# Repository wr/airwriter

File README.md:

# AirWriter

AirPrint for your vintage Apple printer.

Print from your phone or computer to an Apple ImageWriter, StyleWriter or LaserWriter. Connect
AirWriter to the printer and your Wi-Fi, and the printer shows up like any other. Nothing to
install.

The top is a gold-plated circuit board with 37 lights glowing through it. A rainbow sweeps
across when it starts up, and a few dots glow like fireflies while it's idle.

- **Five-minute setup.** All from your phone.
- **Color.** If your printer does color, so does AirWriter.
- **Vintage Macs too.** Print from a vintage Mac over a LocalTalk cable or your network, or from
  an emulator like Infinite Mac.
- **Up to six printers.** One AirWriter shares them all.
- **Open source.** Hardware and software, free to tinker with.

Buy one from [Wells Workshop](https://shop.wells.ee/products/airwriter).

## What you need

- A vintage Apple printer ([check yours](../../wiki/Supported-Printers))
- The cable your printer uses with a Mac ([which cable](../../wiki/Troubleshooting#crossover-cable))
- A USB-C charger
- 2.4 GHz Wi-Fi

The [wiki](../../wiki) has setup help and troubleshooting. [Updates](../../releases) install over
Wi-Fi.

Questions? Ask in [Wells Workshop on Discord](https://discord.gg/gACNgfyB7k), where other builders can help too. Found a bug or want a feature? Open an [issue](https://github.com/wr/airwriter/issues).

## How it works

Inside is an ESP32-S3. It shows each printer to your network as an AirPrint printer. Each page
goes out in the printer's own language, down the printer cable or over AppleTalk. LocalTalk runs
on Tashtari's TashTalk, on a small PIC chip.

| Path | Contents |
|---|---|
| `firmware/` | ESP-IDF application (ESP32-S3) |
| `tools/` | Host builds of the raster and IPP code, tests, fixtures and the settings page |
| `hardware/` | KiCad board and front panel |
| `enclosure/` | Case and light-guide lattice in build123d, with printable STLs in `out/` |

Firmware builds with ESP-IDF 5.5 (`idf.py -C firmware build`). Host tests run anywhere with a C
compiler: `make -C tools/rip test regress` and `make -C tools/ipp test`. `AGENTS.md` has the full
toolchain notes.

## Credits

LocalTalk runs on Tashtari's [TashTalk](https://github.com/lampmerchant/tashtalk). Monroe
Williams worked out the StyleWriter's serial protocol in the 1990s and wrote
[lpstyl](https://github.com/Godzil/lpstyl). FeralFirmware took Apple's StyleWriter and LaserWriter 300
drivers apart for [TailTalk](https://github.com/FeralFirmware/TailTalk) and InkTalk. Thank you all.

## License

Firmware and tools are GPL-3.0-or-later, hardware and enclosure CERN-OHL-S-2.0, docs CC-BY-SA-4.0.
See [`LICENSE.md`](LICENSE.md), which also covers third-party material.

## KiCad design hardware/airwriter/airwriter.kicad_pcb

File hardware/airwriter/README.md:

# AirWriter hardware

KiCad 10 project. Two-layer, 1.6mm FR4, 1oz copper, HASL.

**Board is 32 x 54mm.** The spec targeted 55 x 35mm (1925mm²); this is 1728mm².
Three parts set the floor and none of them can shrink:

- the ESP32-S3-WROOM-1 needs 18 x 19.5mm of board with its antenna overhanging the top edge
- the mini-DIN body reserves the entire bottom 13.5mm
- the USB-C receptacle sits beside it on the same edge

## Status

| Stage | State |
|---|---|
| Schematic | Complete. ERC clean, zero errors. 52 footprints, both ports. |
| Routing | Complete. 434 segments, 34 vias. **Every component pad connected.** |
| DRC | 5, all cosmetic. 15 unconnected, all pour-fragment to pour-fragment, none involving a pad or track. |
| Fab outputs | Gerbers, Excellon drill + map, BOM, pick-and-place, render, in `fab/`. |

Board is **52 x 54mm**, two layers. Bottom edge carries the printer mini-DIN, the
LocalTalk mini-DIN and USB-C. BOM is 44 populated parts plus 4 DNP.

### What DRC still reports, and why it is fine

- 2 silkscreen-over-edge on U1. The module deliberately overhangs the top edge.
- 3 library metadata mismatches. J2 and J4 because the mini-DIN footprint was injected
  into the board by hand; U1 because its thermal-via drills were deliberately enlarged.
- 15 "unconnected" between GND pour fragments. Every fragment is anchored to GND through
  an adjacent pad or via, so this is zone contiguity rather than floating copper. **No pad
  and no track appears in the unconnected list.**

## Modes

The board supports three, and only the third needed hardware:

1. **AirPrint only** — IPP over WiFi to the printer's serial port.
2. **AirPrint + EtherTalk** — pure firmware, no hardware change. Not yet written.
3. **AirPrint + LocalTalk** — the second mini-DIN, the PIC running TashTalk, and the split
   transceiver. This is AirWriter acting as the AppleTalk option card the ImageWriter never
   had. Firmware not yet written.

Only one AppleTalk transport can be active at a time unless you write an AppleTalk router.
AirPrint runs concurrently with any of them because it is IP.

## Routing

Routed with Freerouting 2.2.4. It cannot be automated: KiCad 10 dropped Specctra DSN export and
SES import from `kicad-cli`, so the round trip is GUI-only. Freerouting lives at
`~/.local/share/freerouting/freerouting.jar` and Java 25 is present. To re-route:

1. Open the PCB, File > Export > Specctra DSN
2. `java -jar ~/.local/share/freerouting/freerouting.jar -de board.dsn -do board.ses`
3. File > Import > Specctra Session

**After any re-route, always run DRC with `--refill-zones`.** Freerouting does not repour the GND
zone, and an unfilled zone produces hundreds of phantom clearance errors — 278 violations that
drop to 3 once refilled.

## Fab: PCBWay

Order as: **32 x 54mm, 2 layer, 1.6mm FR4, 1oz copper, HASL**. Nothing here needs a premium
process.

The design is held to PCBWay's cost-effective tier on purpose:

| Parameter | This board | PCBWay |
|---|---|---|
| Min drill | 0.30mm | 0.30mm standard. **0.20mm is an upgraded spec and costs a lot more** |
| Min track / space | 0.20mm actual, 0.15mm rule | 0.076mm possible, 0.15mm recommended to save cost |
| Copper to board edge | 0.2665mm worst case | under 0.20mm gets flagged |
| Via | 0.6mm pad / 0.3mm drill | standard |

**The 0.30mm drill floor is the one to protect.** KiCad's stock ESP32-S3-WROOM-1 footprint puts
twelve 0.20mm thermal vias in its ground pad, which would drop the whole board into PCBWay's
advanced tier — a documented case went from $5 to $65 for ten boards. Those twelve drills were
enlarged to 0.30mm in the board file. The 0.6mm pad still leaves a 0.15mm annular ring.

That edit lives in the board, not in KiCad's library, so **re-importing U1's footprint from the
library will silently put the 0.20mm drills back**. It is also why U1 shows a library mismatch in
DRC. Check the drill table before every order:

```
kicad-cli pcb export drill --output fab/ --format excellon airwriter.kicad_pcb
grep -E '^T[0-9]+C' fab/airwriter.drl     # nothing below 0.300
```

BOM carries manufacturer part numbers for the actives and connectors. Passives are specified by
value, package, dielectric and voltage with "or equivalent", which PCBWay sources normally.

## Toolchain notes

`kicad-cli` is not on PATH: `/Applications/KiCad/KiCad.app/Contents/MacOS/kicad-cli` (10.0.2).

Three traps hit while building this, all worth remembering:

- **`set_design_rules` (konnect MCP) corrupts this board.** KiCad 10 keeps DRC constraints in
  `.kicad_pro`, but the tool writes them into the `.kicad_pcb` setup block, duplicating keys and
  making the board unloadable. Edit `airwriter.kicad_pro` instead.
- **`set_board_size` appends an outline rather than replacing it.** Calling it twice leaves two
  overlapping rectangles on Edge.Cuts.
- **The konnect placement tools resolve `lib_id` only against KiCad's install directory**, ignoring
  project and global library tables. The project libraries are symlinked into the app bundle as a
  workaround; those symlinks vanish on a KiCad upgrade and need recreating.

`min_through_hole_diameter` is set to 0.2mm because the WROOM-1 footprint uses 0.2mm thermal vias
in its ground pad. That is within JLCPCB capability.

## Deviations from the spec

- **U2 is a MAX3490ESA+ (SOIC-8), not a MAX3491ESD+ (SOIC-14).** The spec tied DE high and RE low
  permanently, so the MAX3491's enable pins were dead weight. The MAX3490 is the same full-duplex
  RS-422 transceiver without them, and it ships with a verified pinout in KiCad's stock library.
- **No polarity jumpers at all.** The spec wanted them so the RS-422 pairs could be swapped
  without a respin. The ESP32 UART does the same job in firmware — `uart_set_line_inverse()`
  with `UART_SIGNAL_TXD_INV` / `UART_SIGNAL_RXD_INV`. Inverting DI flips Y and Z together,
  which is electrically identical to swapping the pair. Four parts saved, insurance kept.
- **Receiver polarity corrected.** Spec 2.4 mapped A<-TxD- and B<-TxD+, which inverts every
  received byte. Apple's convention is that a binary 1 has TxD- more negative than TxD+, so
  the + line is non-inverting: A<-TxD+ (pin 6), B<-TxD- (pin 3).
- **R9 added**, a DNP 0R in series with the MAX3232 T1OUT to HSKi path. The spec wanted T1 wired
  but not populated; a DNP series resistor expresses that without U3 driving HSKi by default.
- **SW1 is a B3U-1000P**, not the 4.5mm tactile the spec assumed. The B3S-1100 KiCad offers has a
  10 x 8.9mm courtyard which had become the binding constraint on the pocket beside the mini-DIN.

## Custom library

`lib/airwriter.kicad_sym` and `lib/airwriter.pretty` hold the two parts KiCad does not ship:

- `MiniDIN-8_Kycon_KMDGX-8S-BS_RightAngle` — KiCad has no mini-DIN footprint at all. Geometry taken
  from Kycon engineering drawing KMDGX-xS-BS rev C6 (ECO#18-013), 8-position "Recommended PCB
  Layout (Top View)". Note pin 7 sits at +0.90mm from the centreline while pin 2 directly above it
  sits at +1.30mm — the lower row is deliberately asymmetric.
- `Mini-DIN-8_Shielded` — the stock symbol has no shield pin, so there is no way to net the shell
  for the 0R + 1nF star ground. Pin 9 is SHIELD, tied to all three mounting posts.

## Still to do

1. Add LCSC/Digi-Key ordering codes to the BOM. It currently carries values and footprints only.
2. Optional: 3mm corner radii, which the spec asked for and the outline does not yet have.

## Traps that cost real time here

- **The GND zone was on net `"GND"` while every pad is on `"/GND"`.** KiCad uses the hierarchical
  name with a leading slash. The pour was floating for its entire life and DRC reported it as 28
  isolated-copper islands rather than as a disconnected zone. Check zone nets by string.
- **Footprint zones store absolute coordinates.** Moving a footprint by editing `(at ...)` in a
  script moves the pads but strands any keepout polygon. The WROOM-1 antenna keepout sat 46mm off
  the board until corrected, so DRC was never enforcing it.
- **Freerouting does not repour zones.** Always DRC with `--refill-zones`.

## Trademarks

AirPrint, AppleTalk, LocalTalk, EtherTalk and ImageWriter are trademarks of Apple Inc.
AirWriter is an independent project and is not affiliated with, authorised, sponsored or
endorsed by Apple Inc. These marks are used only descriptively, to state what the board
interoperates with.

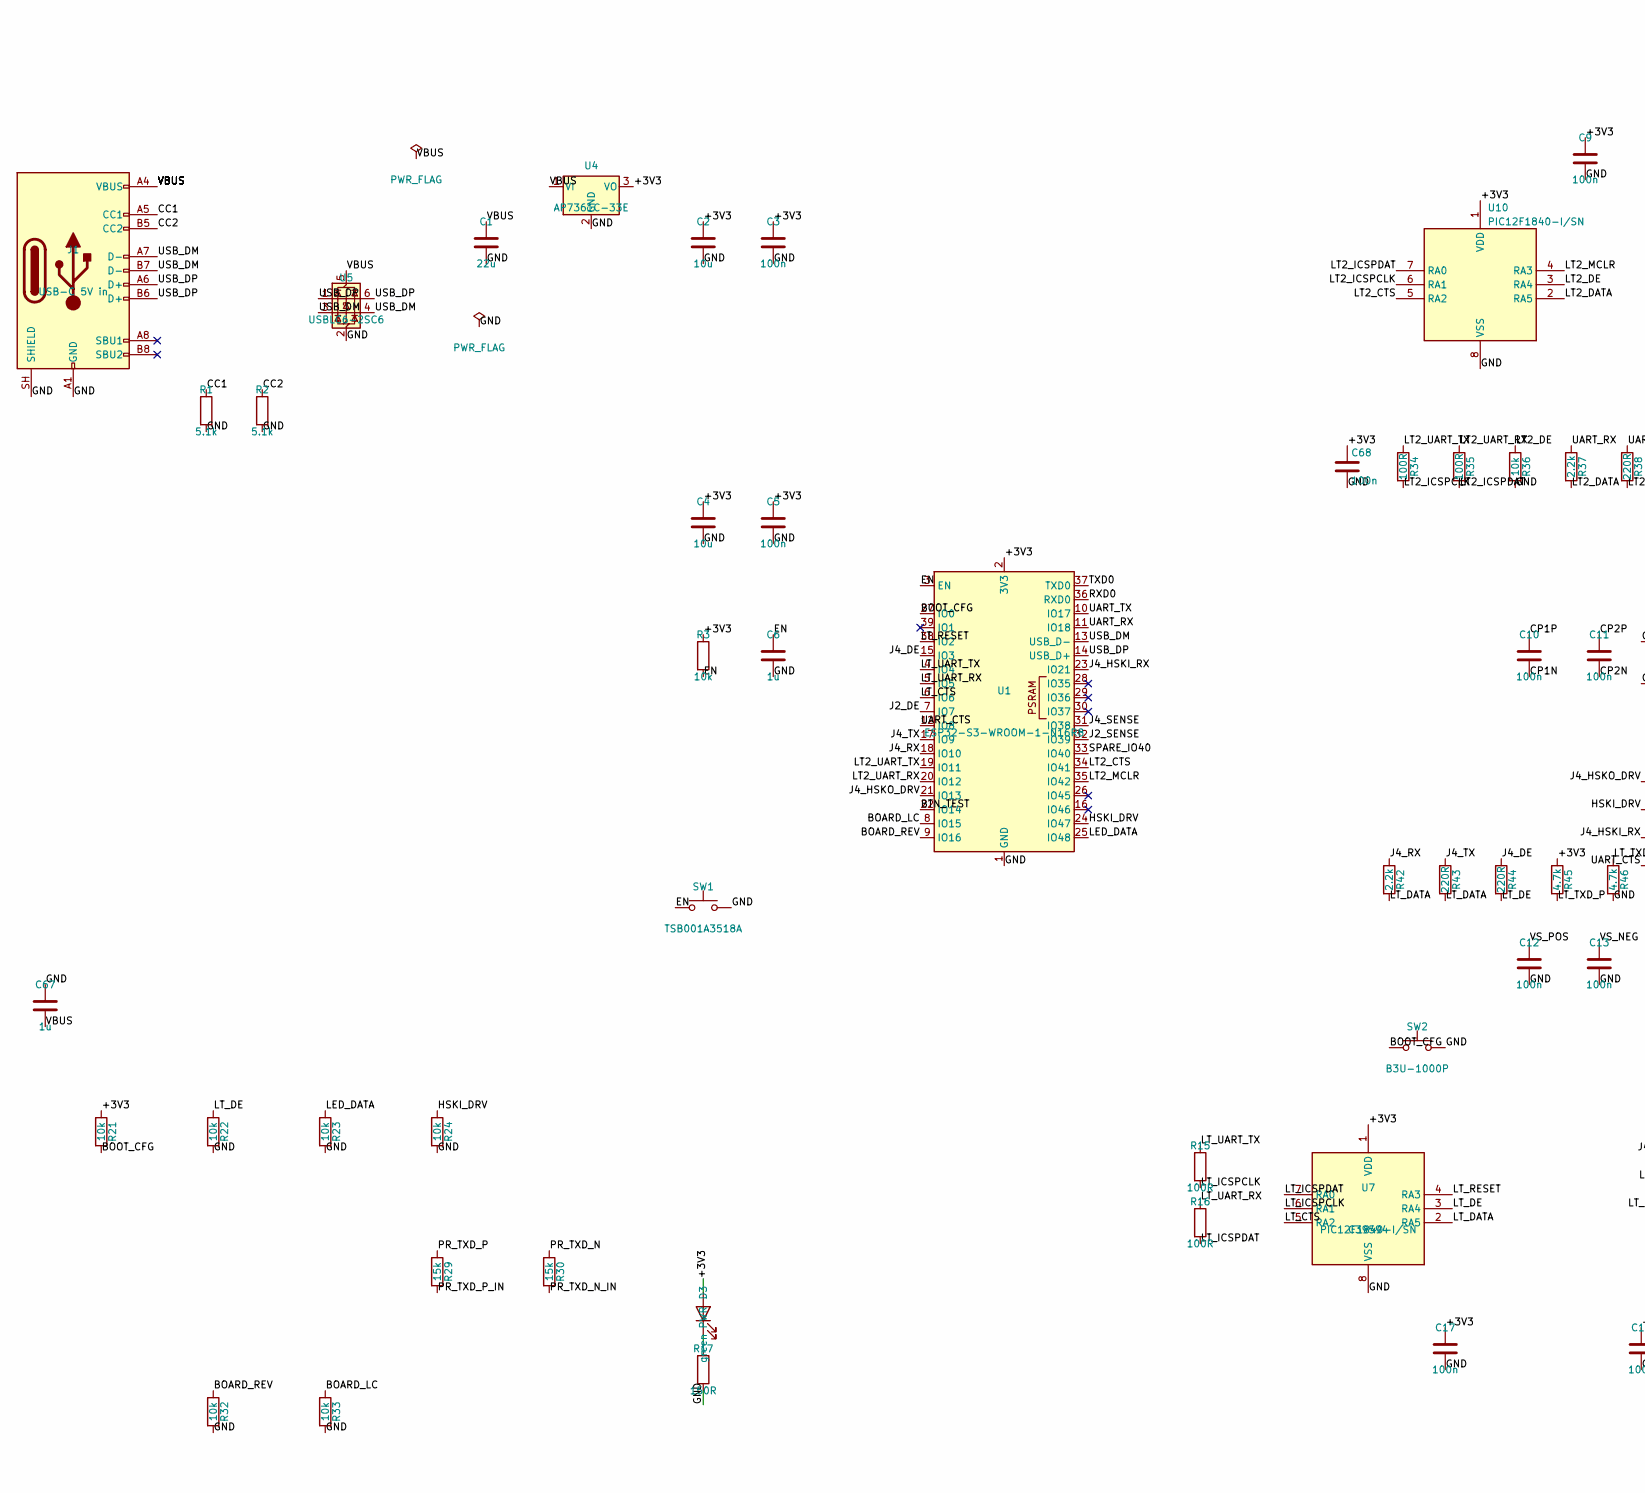
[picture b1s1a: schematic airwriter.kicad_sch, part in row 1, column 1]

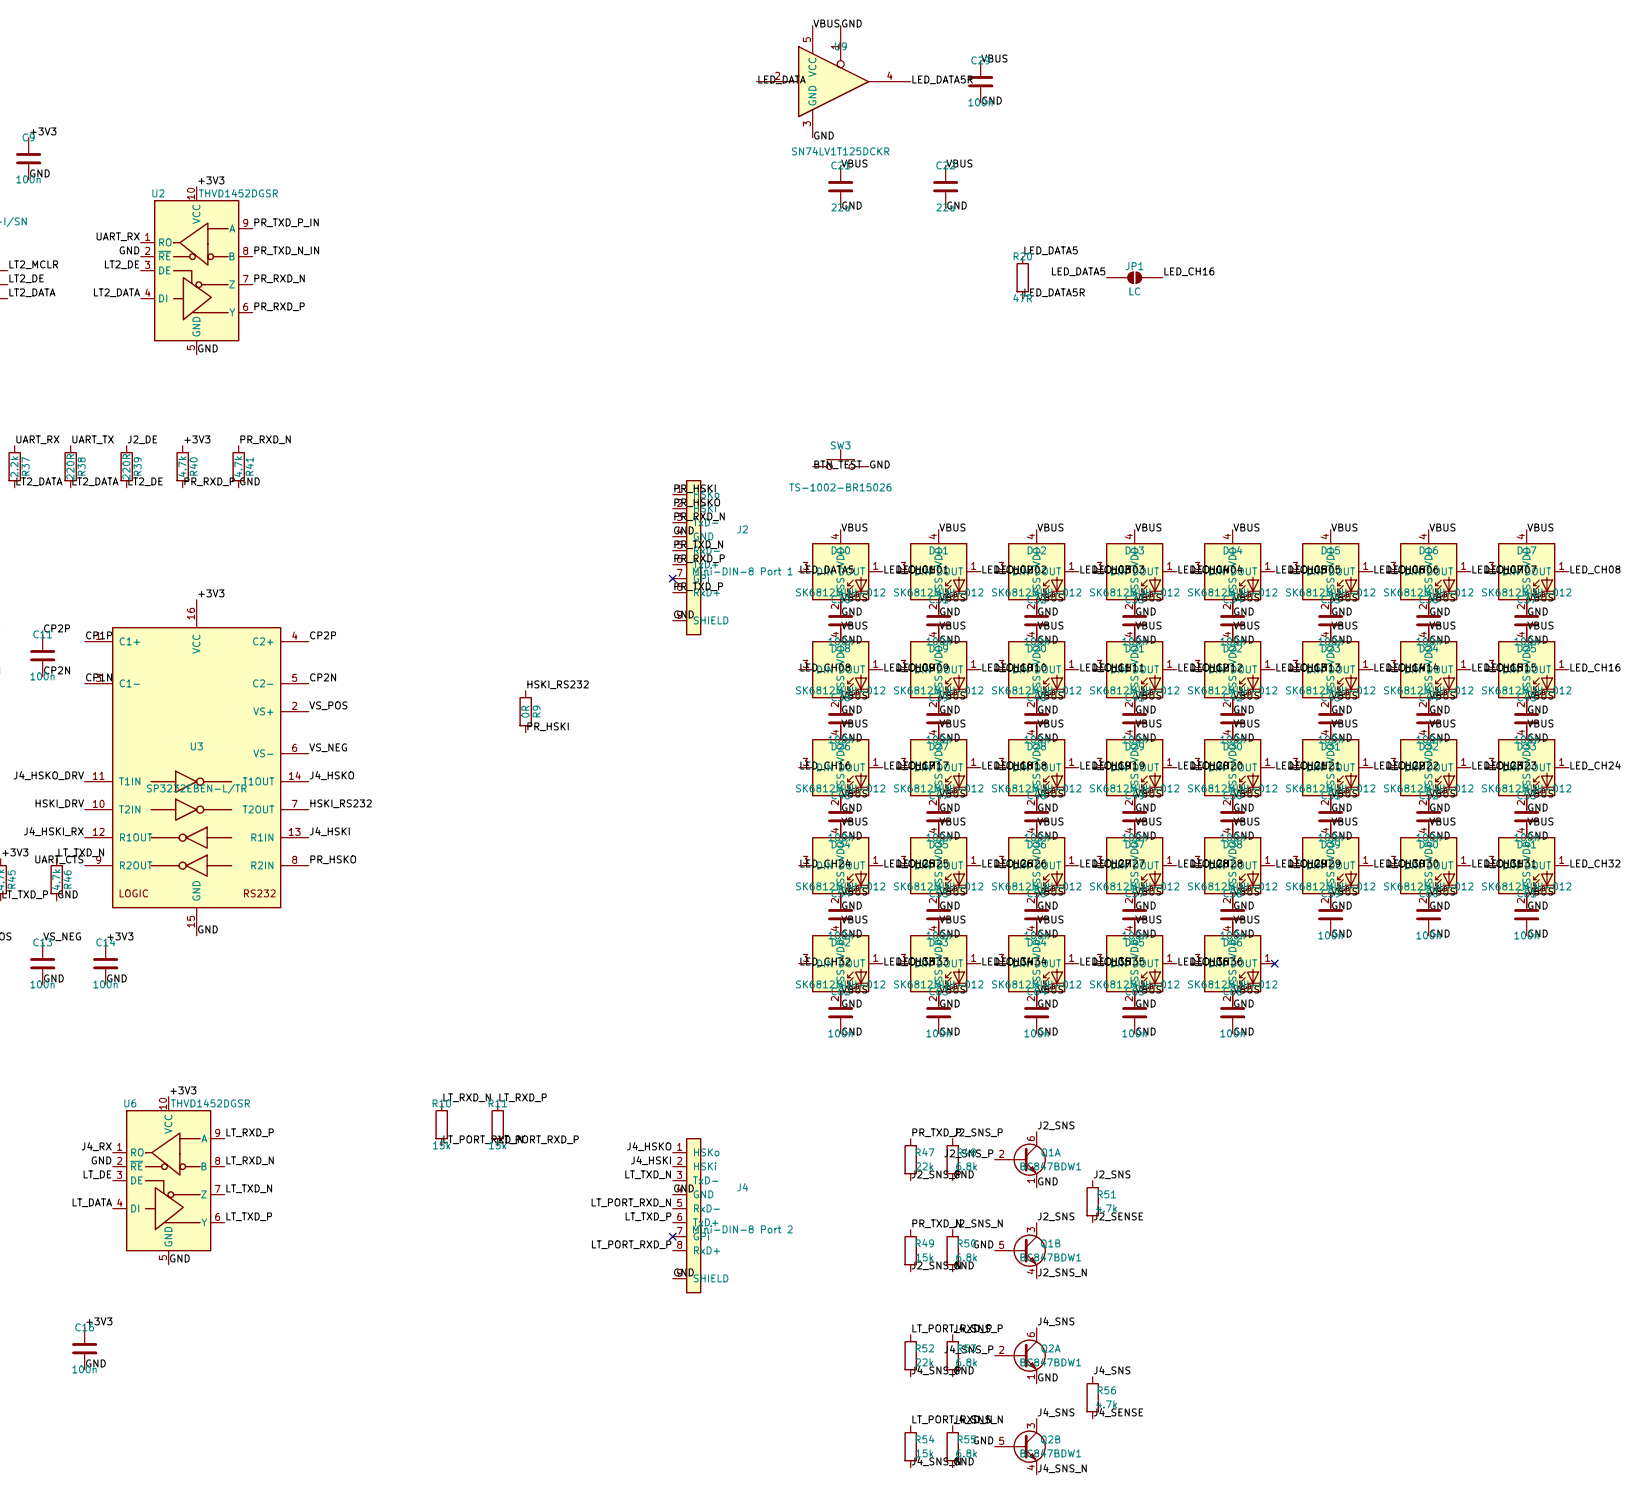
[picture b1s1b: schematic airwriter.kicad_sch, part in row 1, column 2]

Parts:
C1, C21, C22: 22u; C_0805_2012Metric; LCSC C29277
C2, C4: 10u; C_0805_2012Metric; LCSC C15850
C3, C5, C9, C10, C11, C12, C13, C14, C16, C17, C29, C30, C31, C32, C33, C34, C35, C36, C37, C38, C39, C40, C41, C42, C43, C44, C45, C46, C47, C48, C49, C50, C51, C52, C53, C54, C55, C56, C57, C58, C59, C60, C61, C62, C63, C64, C65, C66, C68: 100n; C_0603_1608Metric; LCSC C14663
C6: 1u; C_0603_1608Metric; LCSC C15849
C67: 1u; C_0805_2012Metric; LCSC C28323
D3: green PWR; LED_D3.0mm_Spacer_H8mm; MPN TJ-L3FPTHBGMCGSFLC2G-A5; LCSC C20613324
D10, D11, D12, D13, D14, D15, D16, D17, D18, D19, D20, D21, D22, D23, D24, D25, D26, D27, D28, D29, D30, D31, D32, D33, D34, D35, D36, D37, D38, D39, D40, D41, D42, D43, D44, D45, D46: SK6812MINI-012; LED_SK6812MINI_PLCC4_3.5x3.5mm_P1.75mm; MPN SK6812MINI-012; LCSC C2886570
J1: USB-C 5V in; USB_C_Receptacle_HRO_TYPE-C-31-M-12; MPN TYPE-C-31-M-12; LCSC C165948
J2: Mini-DIN-8 Port 1; MiniDIN-8_Kycon_KMDGX-8S-BS_RightAngle; MPN KMDGX-8S-BS; LCSC C5780060
J4: Mini-DIN-8 Port 2; MiniDIN-8_Kycon_KMDGX-8S-BS_RightAngle; MPN KMDGX-8S-BS; LCSC C5780060
JP1: LC; SolderJumper-2_P1.3mm_Open_RoundedPad1.0x1.5mm
Q1, Q2: BC847BDW1; SOT-363_SC-70-6; MPN BC847BDW1T1G; LCSC C82368
R1, R2: 5.1k; R_0603_1608Metric; LCSC C23186
R3, R21, R22, R23, R24, R32, R33, R36: 10k; R_0603_1608Metric; LCSC C25804
R9: 0R; R_0603_1608Metric; LCSC C21189
R10, R11, R29, R30: 15k; R_0603_1608Metric; LCSC C22809
R15, R16, R34, R35: 100R; R_0603_1608Metric; LCSC C22775
R17: 150R; R_0603_1608Metric; LCSC C22808
R20: 47R; R_0603_1608Metric; LCSC C23182
R37, R42: 2.2k; R_0603_1608Metric; LCSC C4190
R38, R39, R43, R44: 220R; R_0603_1608Metric; LCSC C22962
R40, R41, R45, R46: 4.7k; R_0603_1608Metric; LCSC C23162
R47, R52: 22k; R_0402_1005Metric; LCSC C25768
R48, R50, R53, R55: 6.8k; R_0402_1005Metric; LCSC C25917
R49, R54: 15k; R_0402_1005Metric; LCSC C25756
R51, R56: 4.7k; R_0402_1005Metric; LCSC C25900
SW1: TSB001A3518A; SW_BZCN_TSB001A3518A; MPN TSB001A3518A; LCSC C2888448
SW2: B3U-1000P; SW_SPST_B3U-1000P; LCSC C231329
SW3: TS-1002-BR15026; SW_PUSH_6mm_H13mm; MPN TS-1002-BR15026; LCSC C920209
U1: ESP32-S3-WROOM-1-N16R8; ESP32-S3-WROOM-1; MPN ESP32-S3-WROOM-1-N16R8; LCSC C2913202
U2, U6: THVD1452DGSR; MSOP-10_3x3mm_P0.5mm; MPN THVD1452DGSR; LCSC C2879202
U3: SP3232EBEN-L/TR; SOIC-16_3.9x9.9mm_P1.27mm; MPN SP3232EBEN-L/TR; LCSC C6852
U4: AP7361C-33E; SOT-223-3_TabPin2; MPN AP7361C-33E-13; LCSC C500795
U5: USBLC6-2SC6; SOT-23-6; MPN USBLC6-2SC6; LCSC C7519
U7, U10: PIC12F1840-I/SN; SOIC-8_3.9x4.9mm_P1.27mm; MPN PIC12F1840-I/SN; LCSC C39594
U9: SN74LV1T125DCKR; SOT-353_SC-70-5; MPN SN74LV1T125DCKR; LCSC C75925

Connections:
/+3V3: C2.1, C3.1, C4.1, C5.1, C9.1, C14.1, C16.1, C17.1, C68.1, D3.2 (A), R3.1, R21.1, R40.1, R45.1, U1.2 (3V3), U2.10 (VCC), U3.16 (VCC), U4.3 (VO), U6.10 (VCC), U7.1 (VDD), U10.1 (VDD); also elsewhere on the board
/BOARD_LC: R33.1, U1.8 (IO15)
/BOARD_REV: R32.1, U1.9 (IO16)
/BOOT_CFG: R21.2, SW2.1, U1.27 (IO0)
/BTN_TEST: SW3.1, U1.22 (IO14)
/CC1: J1.A5 (CC1), R1.1
/CC2: J1.B5 (CC2), R2.1
/CP1N: C10.2, U3.3 (C1-)
/CP1P: C10.1, U3.1 (C1+)
/CP2N: C11.2, U3.5 (C2-)
/CP2P: C11.1, U3.4 (C2+)
/EN: C6.1, R3.2, SW1.1, U1.3 (EN); also elsewhere on the board
/HSKI_DRV: R24.1, U1.24 (IO47), U3.10 (T2IN)
/HSKI_RS232: R9.1, U3.7 (T2OUT)
/J2_DE: R39.1, U1.7 (IO7)
/J2_SENSE: R51.2, U1.32 (IO39); also elsewhere on the board
/J2_SNS: Q1.3 (C2), Q1.6 (C1), R51.1
/J2_SNS_N: Q1.4 (E2), R49.2, R50.1
/J2_SNS_P: Q1.2 (B1), R47.2, R48.1
/J4_DE: R44.1, U1.15 (IO3)
/J4_HSKI: J4.2 (HSKi), U3.13 (R1IN)
/J4_HSKI_RX: U1.23 (IO21), U3.12 (R1OUT)
/J4_HSKO: J4.1 (HSKo), U3.14 (T1OUT)
/J4_HSKO_DRV: U1.21 (IO13), U3.11 (T1IN)
/J4_RX: R42.1, U1.18 (IO10), U6.1 (RO)
/J4_SENSE: R56.2, U1.31 (IO38); also elsewhere on the board
/J4_SNS: Q2.3 (C2), Q2.6 (C1), R56.1
/J4_SNS_N: Q2.4 (E2), R54.2, R55.1
/J4_SNS_P: Q2.2 (B1), R52.2, R53.1
/J4_TX: R43.1, U1.17 (IO9)
/LED_CH01: D10.1 (DOUT), D11.3 (DIN)
/LED_CH02: D11.1 (DOUT), D12.3 (DIN)
/LED_CH03: D12.1 (DOUT), D13.3 (DIN)
/LED_CH04: D13.1 (DOUT), D14.3 (DIN)
/LED_CH05: D14.1 (DOUT), D15.3 (DIN)
/LED_CH06: D15.1 (DOUT), D16.3 (DIN)
/LED_CH07: D16.1 (DOUT), D17.3 (DIN)
/LED_CH08: D17.1 (DOUT), D18.3 (DIN)
/LED_CH09: D18.1 (DOUT), D19.3 (DIN)
/LED_CH10: D19.1 (DOUT), D20.3 (DIN)
/LED_CH11: D20.1 (DOUT), D21.3 (DIN)
/LED_CH12: D21.1 (DOUT), D22.3 (DIN)
/LED_CH13: D22.1 (DOUT), D23.3 (DIN)
/LED_CH14: D23.1 (DOUT), D24.3 (DIN)
/LED_CH15: D24.1 (DOUT), D25.3 (DIN)
/LED_CH16: D25.1 (DOUT), D26.3 (DIN), JP1.2 (B)
/LED_CH17: D26.1 (DOUT), D27.3 (DIN)
/LED_CH18: D27.1 (DOUT), D28.3 (DIN)
/LED_CH19: D28.1 (DOUT), D29.3 (DIN)
/LED_CH20: D29.1 (DOUT), D30.3 (DIN)
/LED_CH21: D30.1 (DOUT), D31.3 (DIN)
/LED_CH22: D31.1 (DOUT), D32.3 (DIN)
/LED_CH23: D32.1 (DOUT), D33.3 (DIN)
/LED_CH24: D33.1 (DOUT), D34.3 (DIN)
/LED_CH25: D34.1 (DOUT), D35.3 (DIN)
/LED_CH26: D35.1 (DOUT), D36.3 (DIN)
/LED_CH27: D36.1 (DOUT), D37.3 (DIN)
/LED_CH28: D37.1 (DOUT), D38.3 (DIN)
/LED_CH29: D38.1 (DOUT), D39.3 (DIN)
/LED_CH30: D39.1 (DOUT), D40.3 (DIN)
/LED_CH31: D40.1 (DOUT), D41.3 (DIN)
/LED_CH32: D41.1 (DOUT), D42.3 (DIN)
/LED_CH33: D42.1 (DOUT), D43.3 (DIN)
/LED_CH34: D43.1 (DOUT), D44.3 (DIN)
/LED_CH35: D44.1 (DOUT), D45.3 (DIN)
/LED_CH36: D45.1 (DOUT), D46.3 (DIN)
/LED_DATA: R23.1, U1.25 (IO48), U9.2
/LED_DATA5: D10.3 (DIN), JP1.1 (A), R20.1; also elsewhere on the board
/LED_DATA5R: R20.2, U9.4
/LT2_CTS: U1.34 (IO41), U10.5 (RA2)
/LT2_DATA: R37.2, R38.2, U2.4 (DI), U10.2 (RA5)
/LT2_DE: R36.1, R39.2, U2.3 (DE), U10.3 (RA4)
/LT2_ICSPCLK: R34.2, U10.6 (RA1)
/LT2_ICSPDAT: R35.2, U10.7 (RA0)
/LT2_MCLR: U1.35 (IO42), U10.4 (RA3)
/LT2_UART_RX: R35.1, U1.20 (IO12)
/LT2_UART_TX: R34.1, U1.19 (IO11)
/LT_CTS: U1.6 (IO6), U7.5 (RA2)
/LT_DATA: R42.2, R43.2, U6.4 (DI), U7.2 (RA5)
/LT_DE: R22.1, R44.2, U6.3 (DE), U7.3 (RA4)
/LT_ICSPCLK: R15.2, U7.6 (RA1)
/LT_ICSPDAT: R16.2, U7.7 (RA0)
/LT_PORT_RXD_N: J4.5 (RxD-), R10.2, R54.1
/LT_PORT_RXD_P: J4.8 (RxD+), R11.2, R52.1
/LT_RESET: U1.38 (IO2), U7.4 (RA3)
/LT_RXD_N: R10.1, U6.8 (B)
/LT_RXD_P: R11.1, U6.9 (A)
/LT_TXD_N: J4.3 (TxD-), R46.1, U6.7 (Z)
/LT_TXD_P: J4.6 (TxD+), R45.2, U6.6 (Y)
/LT_UART_RX: R16.1, U1.5 (IO5)
/LT_UART_TX: R15.1, U1.4 (IO4)
/PR_HSKI: J2.1 (HSKo), R9.2
/PR_HSKO: J2.2 (HSKi), U3.8 (R2IN)
/PR_RXD_N: J2.3 (TxD-), R41.1, U2.7 (Z)
/PR_RXD_P: J2.6 (TxD+), R40.2, U2.6 (Y)
/PR_TXD_N: J2.5 (RxD-), R30.1, R49.1
/PR_TXD_N_IN: R30.2, U2.8 (B)
/PR_TXD_P: J2.8 (RxD+), R29.1, R47.1
/PR_TXD_P_IN: R29.2, U2.9 (A)
/RXD0: U1.36 (RXD0); also elsewhere on the board
/SPARE_IO40: U1.33 (IO40); also elsewhere on the board
/TXD0: U1.37 (TXD0); also elsewhere on the board
/UART_CTS: U1.12 (IO8), U3.9 (R2OUT)
/UART_RX: R37.1, U1.11 (IO18), U2.1 (RO)
/UART_TX: R38.1, U1.10 (IO17)
/USB_DM: J1.A7 (D-), J1.B7 (D-), U1.13 (USB_D-), U5.3 (I/O2), U5.4 (I/O2)
/USB_DP: J1.A6 (D+), J1.B6 (D+), U1.14 (USB_D+), U5.1 (I/O1), U5.6 (I/O1)
/VS_NEG: C13.1, U3.6 (VS-)
/VS_POS: C12.1, U3.2 (VS+)
unnamed: D3.1 (K), R17.1

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
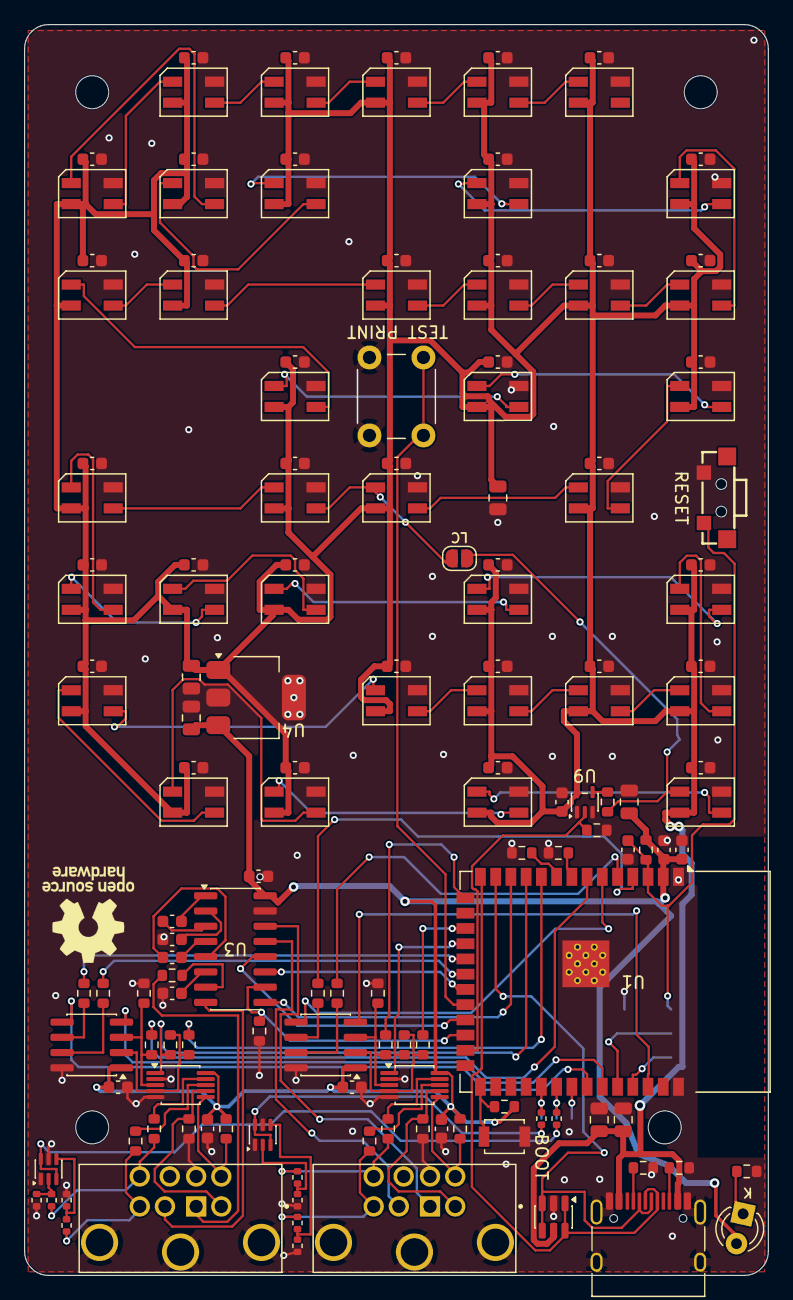
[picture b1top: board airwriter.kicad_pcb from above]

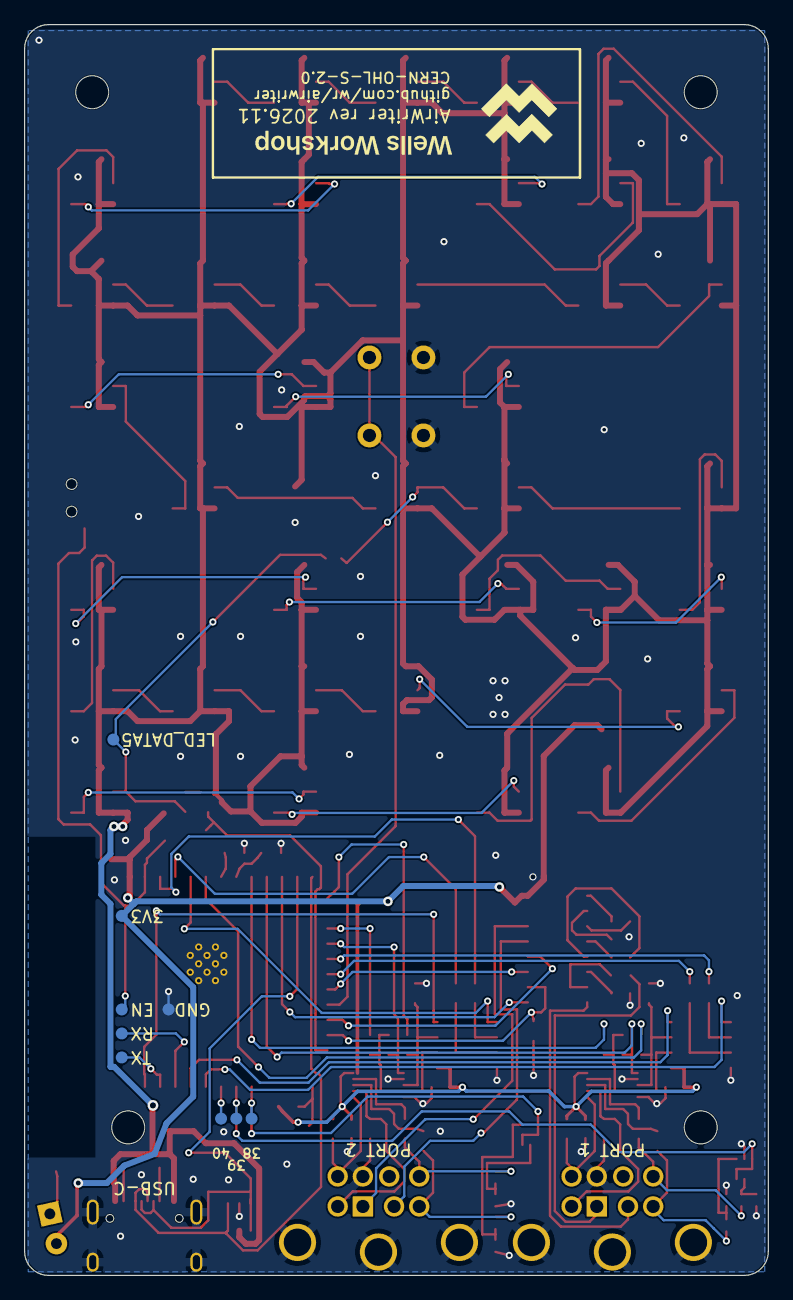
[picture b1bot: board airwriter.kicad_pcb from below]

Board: 2 copper layers, 62.0 x 104.3 mm, 167 parts (9 on the bottom side), 112 nets.

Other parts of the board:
H1, H2, H3, H4: MountingHole_2.2mm_M2
LOGO1: OSHW-Logo_7.5x8mm_SilkScreen
TP2: +3V3; TestPoint_Pad_D1.0mm
TP4: EN; TestPoint_Pad_D1.0mm
TP5: LED_DATA5; TestPoint_Pad_D1.0mm
TP7: TXD0; TestPoint_Pad_D1.0mm
TP8: RXD0; TestPoint_Pad_D1.0mm
TP9: GND; TestPoint_Pad_D1.0mm
TP10: J4_SENSE; SparePad_D1.0mm
TP11: J2_SENSE; SparePad_D1.0mm
TP12: SPARE_IO40; SparePad_D1.0mm

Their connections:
/+3V3: TP2.1; also elsewhere on the board
/EN: TP4.1; also elsewhere on the board
/J2_SENSE: TP11.1; also elsewhere on the board
/J4_SENSE: TP10.1; also elsewhere on the board
/LED_DATA5: TP5.1; also elsewhere on the board
/RXD0: TP8.1; also elsewhere on the board
/SPARE_IO40: TP12.1; also elsewhere on the board
/TXD0: TP7.1; also elsewhere on the board

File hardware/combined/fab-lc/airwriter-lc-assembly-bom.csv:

Designator,Comment,Footprint,LCSC,Qty,Note
"C1,C22",22u,Capacitor_SMD:C_0805_2012Metric,C29277,2,
"C2,C4",10u,Capacitor_SMD:C_0805_2012Metric,C15850,2,
"C3,C5,C9,C10,C11,C12,C13,C14,C16,C17,C29,C46,C68",100n,Capacitor_SMD:C_0603_1608Metric,C14663,13,
C6,1u,Capacitor_SMD:C_0603_1608Metric,C15849,1,
C67,1u,Capacitor_SMD:C_0805_2012Metric,C28323,1,
D3,green PWR,airwriter:LED_D3.0mm_Spacer_H8mm,C20613324,1,"THT: 3 mm flat-top green on a HIWA LED4*8 nylon spacer (LCSC C92326) under the body, lens up"
D26,SK6812MINI-012,LED_SMD:LED_SK6812MINI_PLCC4_3.5x3.5mm_P1.75mm,C2886570,1,
J1,USB-C 5V in,Connector_USB:USB_C_Receptacle_HRO_TYPE-C-31-M-12,C165948,1,
"R1,R2",5.1k,Resistor_SMD:R_0603_1608Metric,C23186,2,
"R3,R21-R24,R32,R33,R36",10k,Resistor_SMD:R_0603_1608Metric,C25804,8,
R9,0R,Resistor_SMD:R_0603_1608Metric,C21189,1,
"R10,R11,R29,R30",15k,Resistor_SMD:R_0603_1608Metric,C22809,4,
"R15,R16,R34,R35",100R,Resistor_SMD:R_0603_1608Metric,C22775,4,
R17,150R,Resistor_SMD:R_0603_1608Metric,C22808,1,
R20,47R,Resistor_SMD:R_0603_1608Metric,C23182,1,
"R37,R42",2.2k,Resistor_SMD:R_0603_1608Metric,C4190,2,
"R38,R39,R43,R44",220R,Resistor_SMD:R_0603_1608Metric,C22962,4,
"R40,R41,R45,R46",4.7k,Resistor_SMD:R_0603_1608Metric,C23162,4,
SW1,TSB001A3518A,airwriter:SW_BZCN_TSB001A3518A,C2888448,1,
SW2,B3U-1000P,Button_Switch_SMD:SW_SPST_B3U-1000P,C231329,1,
SW3,TS-1002-BR15026,Button_Switch_THT:SW_PUSH_6mm_H13mm,C920209,1,
U1,ESP32-S3-WROOM-1-N16R8,RF_Module:ESP32-S3-WROOM-1,C2913202,1,
"U2,U6",THVD1452DGSR,Package_SO:MSOP-10_3x3mm_P0.5mm,C2879202,2,
U3,SP3232EBEN-L/TR,Package_SO:SOIC-16_3.9x9.9mm_P1.27mm,C6852,1,
U4,AP7361C-33E,Package_TO_SOT_SMD:SOT-223-3_TabPin2,C500795,1,
U5,USBLC6-2SC6,Package_TO_SOT_SMD:SOT-23-6,C7519,1,
U9,SN74LV1T125DCKR,Package_TO_SOT_SMD:SOT-353_SC-70-5,C75925,1,
D3 (spacer),"LED4*8 nylon LED spacer, 4 mm x 8 mm",-,C92326,1,"Under D3: LED leads through the spacer bore, LED flange seated on it, lens up"
